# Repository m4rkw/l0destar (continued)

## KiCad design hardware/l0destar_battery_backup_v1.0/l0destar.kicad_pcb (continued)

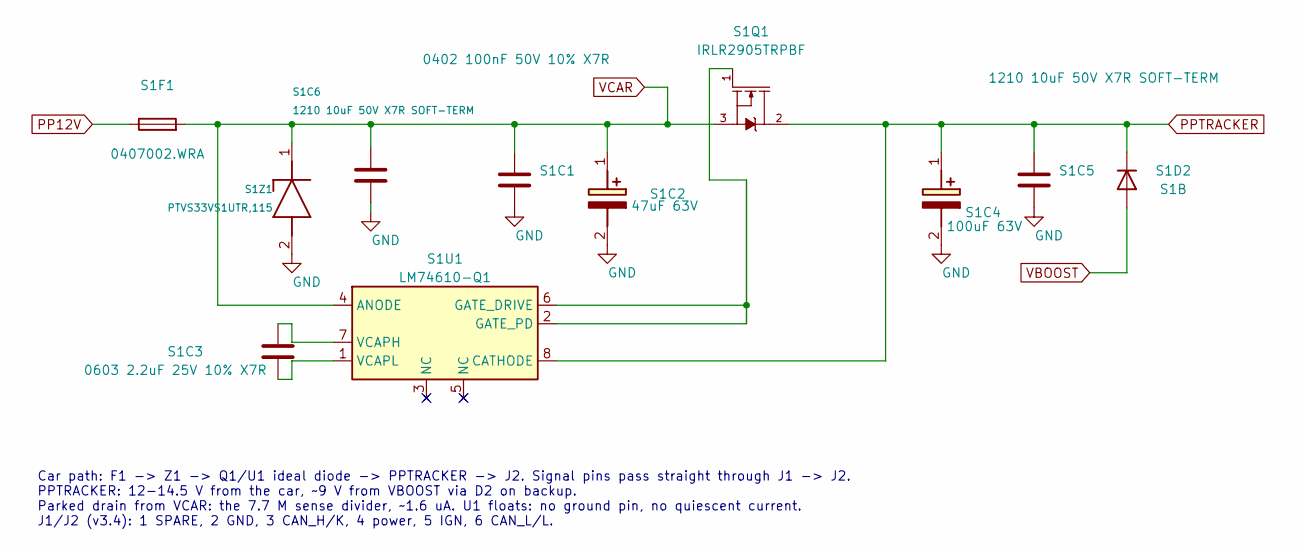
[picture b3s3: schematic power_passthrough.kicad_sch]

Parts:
S1C1: 0402 100nF 50V 10% X7R; C_0402_1005Metric; MPN GRM155R71H104KE14D
S1C2: 47uF 63V; EEE_FK1J470P; MPN EEE-FK1J470P
S1C3: 0603 2.2uF 25V 10% X7R; C_0603_1608Metric; MPN GRM188Z71E225KE43D
S1C4: 100uF 63V; EEEFK1J101P; MPN EEE-FK1J101P
S1C5, S1C6: 1210 10uF 50V X7R SOFT-TERM; C_1210_3225Metric; MPN MCJCU32MLB7106KPPDT1
S1D2: S1B; D_SMA; MPN S1B
S1F1: 0407002.WRA; Fuse_1206_3216Metric; MPN 0407002.WRA
S1Q1: IRLR2905TRPBF
S1U1: LM74610-Q1; VSSOP-8_3x3mm_P0.65mm; MPN LM74610QDGKRQ1
S1Z1: PTVS33VS1UTR,115; Nexperia_CFP3_SOD-123W; MPN PTVS33VS1UTR,115

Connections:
GND: S1C1.2, S1C2.2 (-), S1C4.2 (-), S1C5.2, S1C6.2, S1Z1.2 (A); also elsewhere on the board
unnamed: S1Q1.1, S1U1.2 (GATE_PD), S1U1.6 (GATE_DRIVE)
unnamed: S1C3.1, S1U1.7 (VCAPH)
unnamed: S1C3.2, S1U1.1 (VCAPL)
PP12V: S1F1.1; also elsewhere on the board
PPTRACKER: S1C4.1 (+), S1C5.1, S1D2.1 (K), S1Q1.2, S1Q1.PAD, S1U1.8 (CATHODE); also elsewhere on the board
VBOOST: S1D2.2 (A); also elsewhere on the board
VCAR: S1C1.1, S1C2.1 (+), S1C6.1, S1F1.2, S1Q1.3, S1U1.4 (ANODE), S1Z1.1 (K); also elsewhere on the board

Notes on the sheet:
Car path: F1 -> Z1 -> Q1/U1 ideal diode -> PPTRACKER -> J2. Signal pins pass straight through J1 -> J2. PPTRACKER: 12-14.5 V from the car, ~9 V from VBOOST via D2 on backup. Parked drain from VCAR: the 7.7 M sense divider, ~1.6 uA. U1 floats: no ground pin, no quiescent current. J1/J2 (v3.4): 1 SPA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

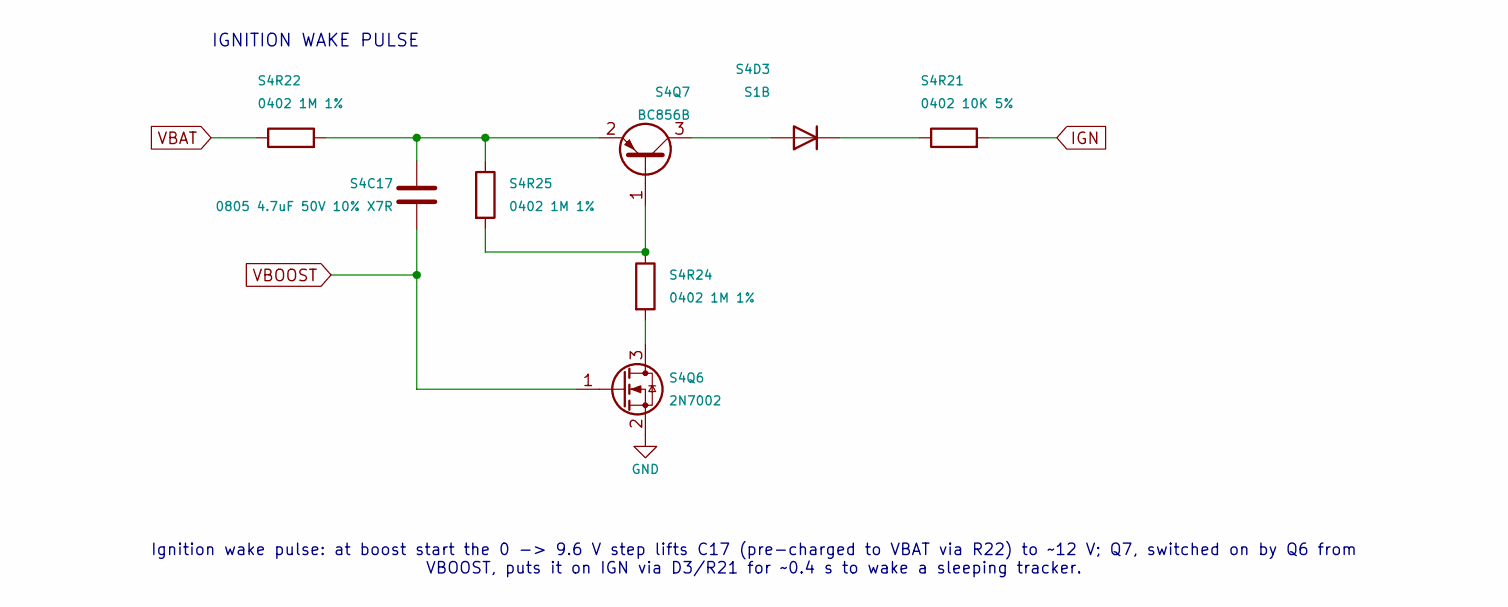
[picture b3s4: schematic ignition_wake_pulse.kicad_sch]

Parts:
S4C17: 0805 4.7uF 50V 10% X7R; C_0805_2012Metric; MPN GRM21BZ71H475KE15K
S4D3: S1B; D_SMA; MPN S1B
S4Q6: 2N7002; SOT-23; MPN 2N7002
S4Q7: BC856B; SOT-23; MPN BC856B
S4R21: 0402 10K 5%; R_0402_1005Metric
S4R22, S4R24, S4R25: 0402 1M 1%; R_0402_1005Metric

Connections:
GND: S4Q6.2 (S); also elsewhere on the board
IGN: S4R21.2; also elsewhere on the board
unnamed: S4D3.2 (A), S4Q7.3 (C)
unnamed: S4D3.1 (K), S4R21.1
unnamed: S4Q6.3 (D), S4R24.2
unnamed: S4Q7.1 (B), S4R24.1, S4R25.2
unnamed: S4C17.1, S4Q7.2 (E), S4R22.2, S4R25.1
VBAT: S4R22.1; also elsewhere on the board
VBOOST: S4C17.2, S4Q6.1 (G); also elsewhere on the board

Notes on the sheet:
IGNITION WAKE PULSE
Ignition wake pulse: at boost start the 0 -> 9.6 V step lifts C17 (pre-charged to VBAT via R22) to ~12 V; Q7, switched on by Q6 from VBOOST, puts it on IGN via D3/R21 for ~0.4 s to wake a sleeping tracker.

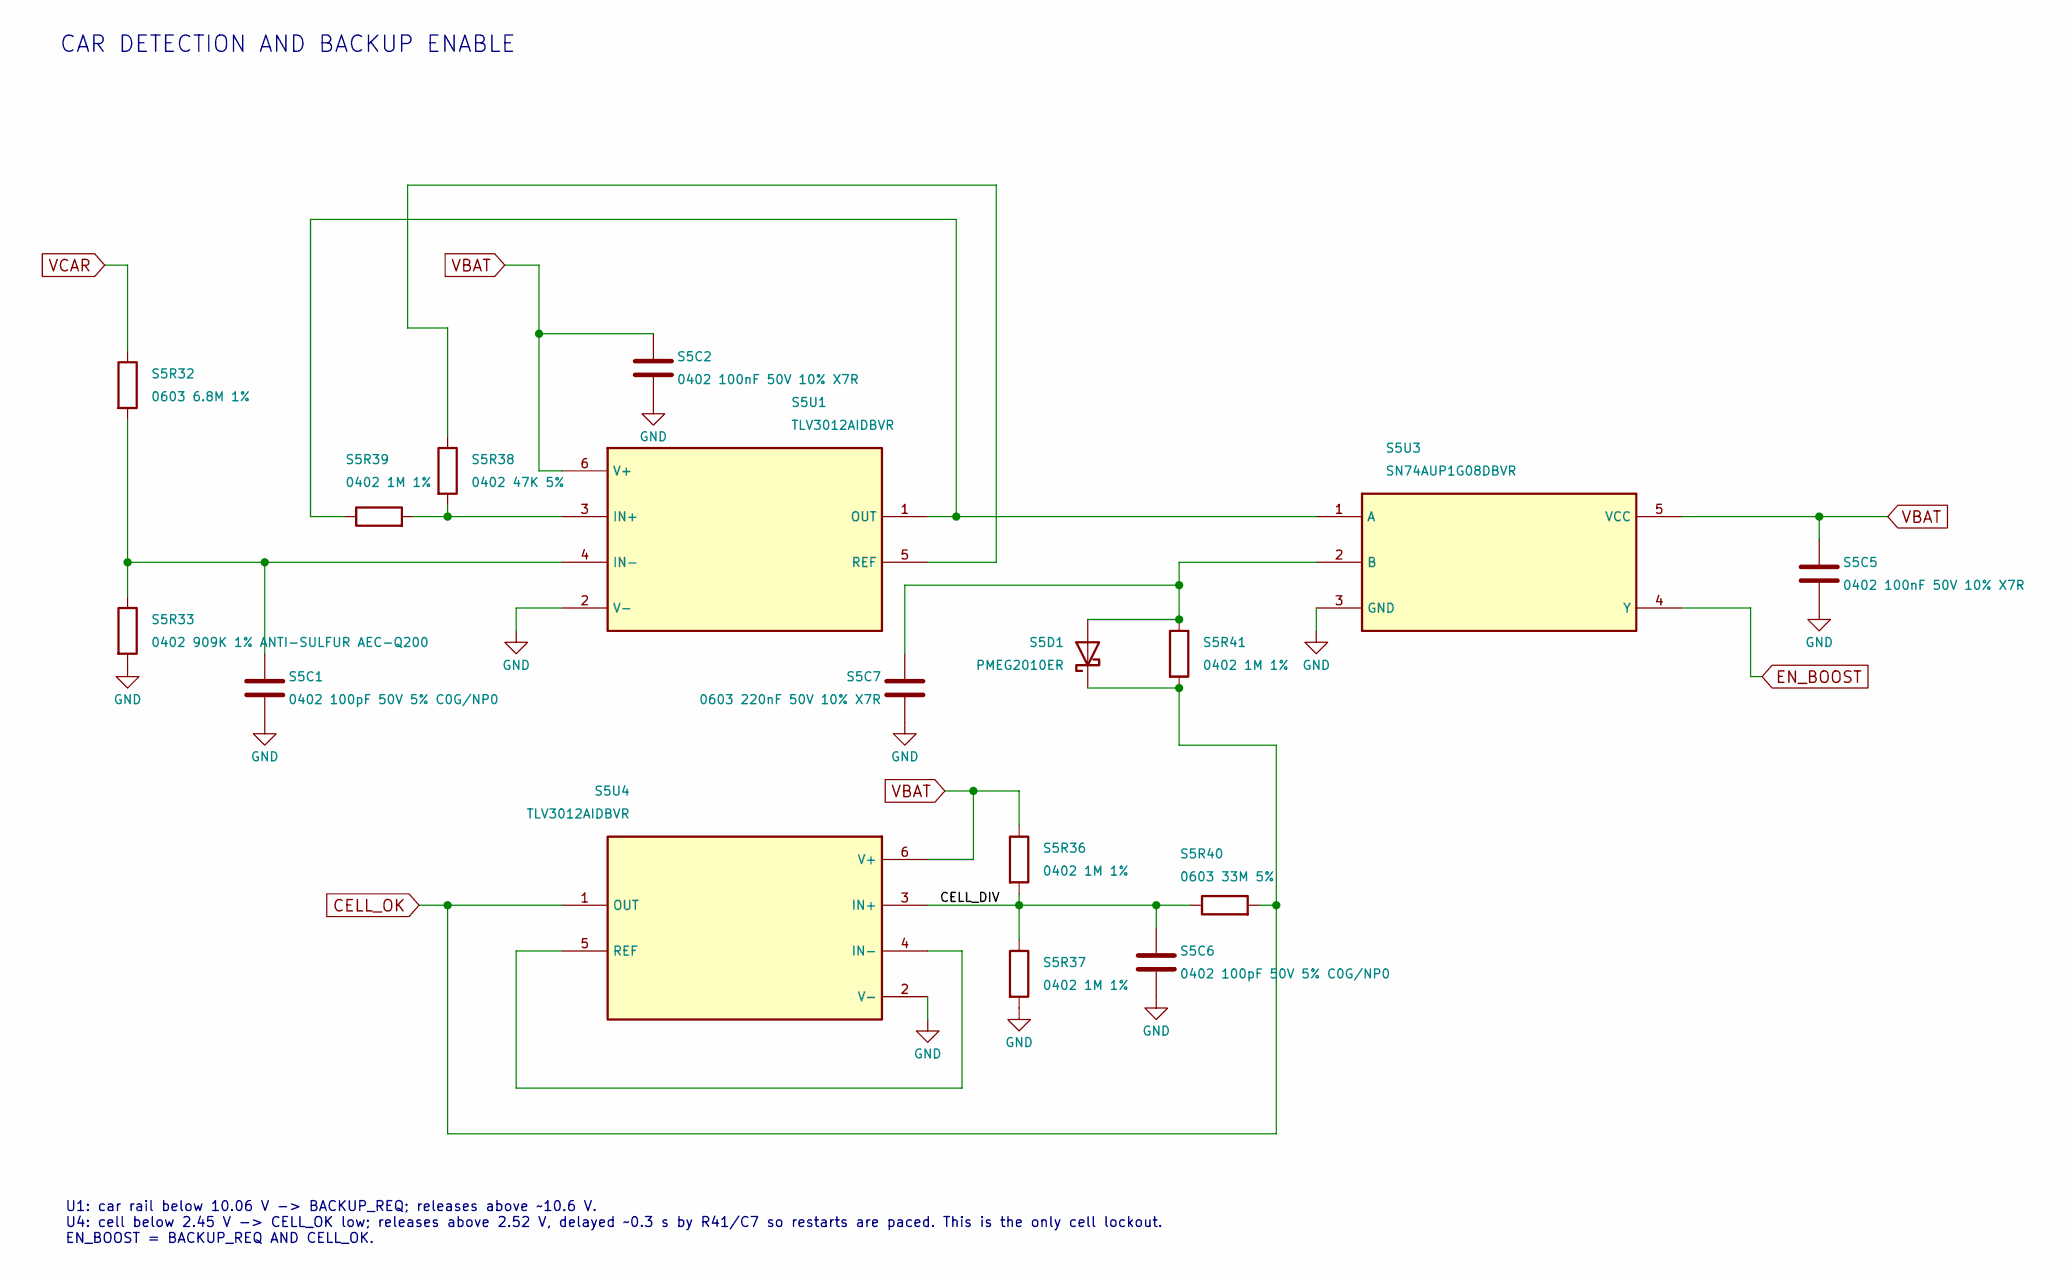
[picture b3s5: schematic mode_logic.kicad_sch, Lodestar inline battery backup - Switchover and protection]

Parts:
S5C1, S5C6: 0402 100pF 50V 5% C0G/NP0; C_0402_1005Metric; MPN 0402N101J500CT
S5C2, S5C5: 0402 100nF 50V 10% X7R; C_0402_1005Metric; MPN GRM155R71H104KE14D
S5C7: 0603 220nF 50V 10% X7R; C_0603_1608Metric
S5D1: PMEG2010ER; Nexperia_CFP3_SOD-123W; MPN PMEG2010ER,115
S5R32: 0603 6.8M 1%; R_0603_1608Metric
S5R33: 0402 909K 1% ANTI-SULFUR AEC-Q200; R_0402_1005Metric; MPN AF0402FR-07909KL
S5R36, S5R37, S5R39, S5R41: 0402 1M 1%; R_0402_1005Metric
S5R38: 0402 47K 5%; R_0402_1005Metric
S5R40: 0603 33M 5%; R_0603_1608Metric
S5U1, S5U4: TLV3012AIDBVR; SOT-23-6; MPN TLV3012AIDBVR
S5U3: SN74AUP1G08DBVR; SOT-23-5; MPN SN74AUP1G08DBVR

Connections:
/Automatic switchover/CELL_DIV: S5C6.1, S5R36.2, S5R37.1, S5R40.1, S5U4.3 (IN+)
CELL_OK: S5D1.1 (K), S5R40.2, S5R41.2, S5U4.1 (OUT)
EN_BOOST: S5U3.4 (Y); also elsewhere on the board
GND: S5C1.2, S5C2.2, S5C5.2, S5C6.2, S5C7.2, S5R33.2, S5R37.2, S5U1.2 (V-), S5U3.3 (GND), S5U4.2 (V-); also elsewhere on the board
unnamed: S5C7.1, S5D1.2 (A), S5R41.1, S5U3.2 (B)
unnamed: S5R38.2, S5R39.2, S5U1.3 (IN+)
unnamed: S5C1.1, S5R32.2, S5R33.1, S5U1.4 (IN-)
unnamed: S5R39.1, S5U1.1 (OUT), S5U3.1 (A)
unnamed: S5R38.1, S5U1.5 (REF)
unnamed: S5U4.4 (IN-), S5U4.5 (REF)
VBAT: S5C2.1, S5C5.1, S5R36.1, S5U1.6 (V+), S5U3.5 (VCC), S5U4.6 (V+); also elsewhere on the board
VCAR: S5R32.1; also elsewhere on the board

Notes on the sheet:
CAR DETECTION AND BACKUP ENABLE
U1: car rail below 10.06 V -> BACKUP_REQ; releases above ~10.6 V. U4: cell below 2.45 V -> CELL_OK low; releases above 2.52 V, delayed ~0.3 s by R41/C7 so restarts are paced. This is the only cell lockout. EN_BOOST = BACKUP_REQ AND CELL_OK.

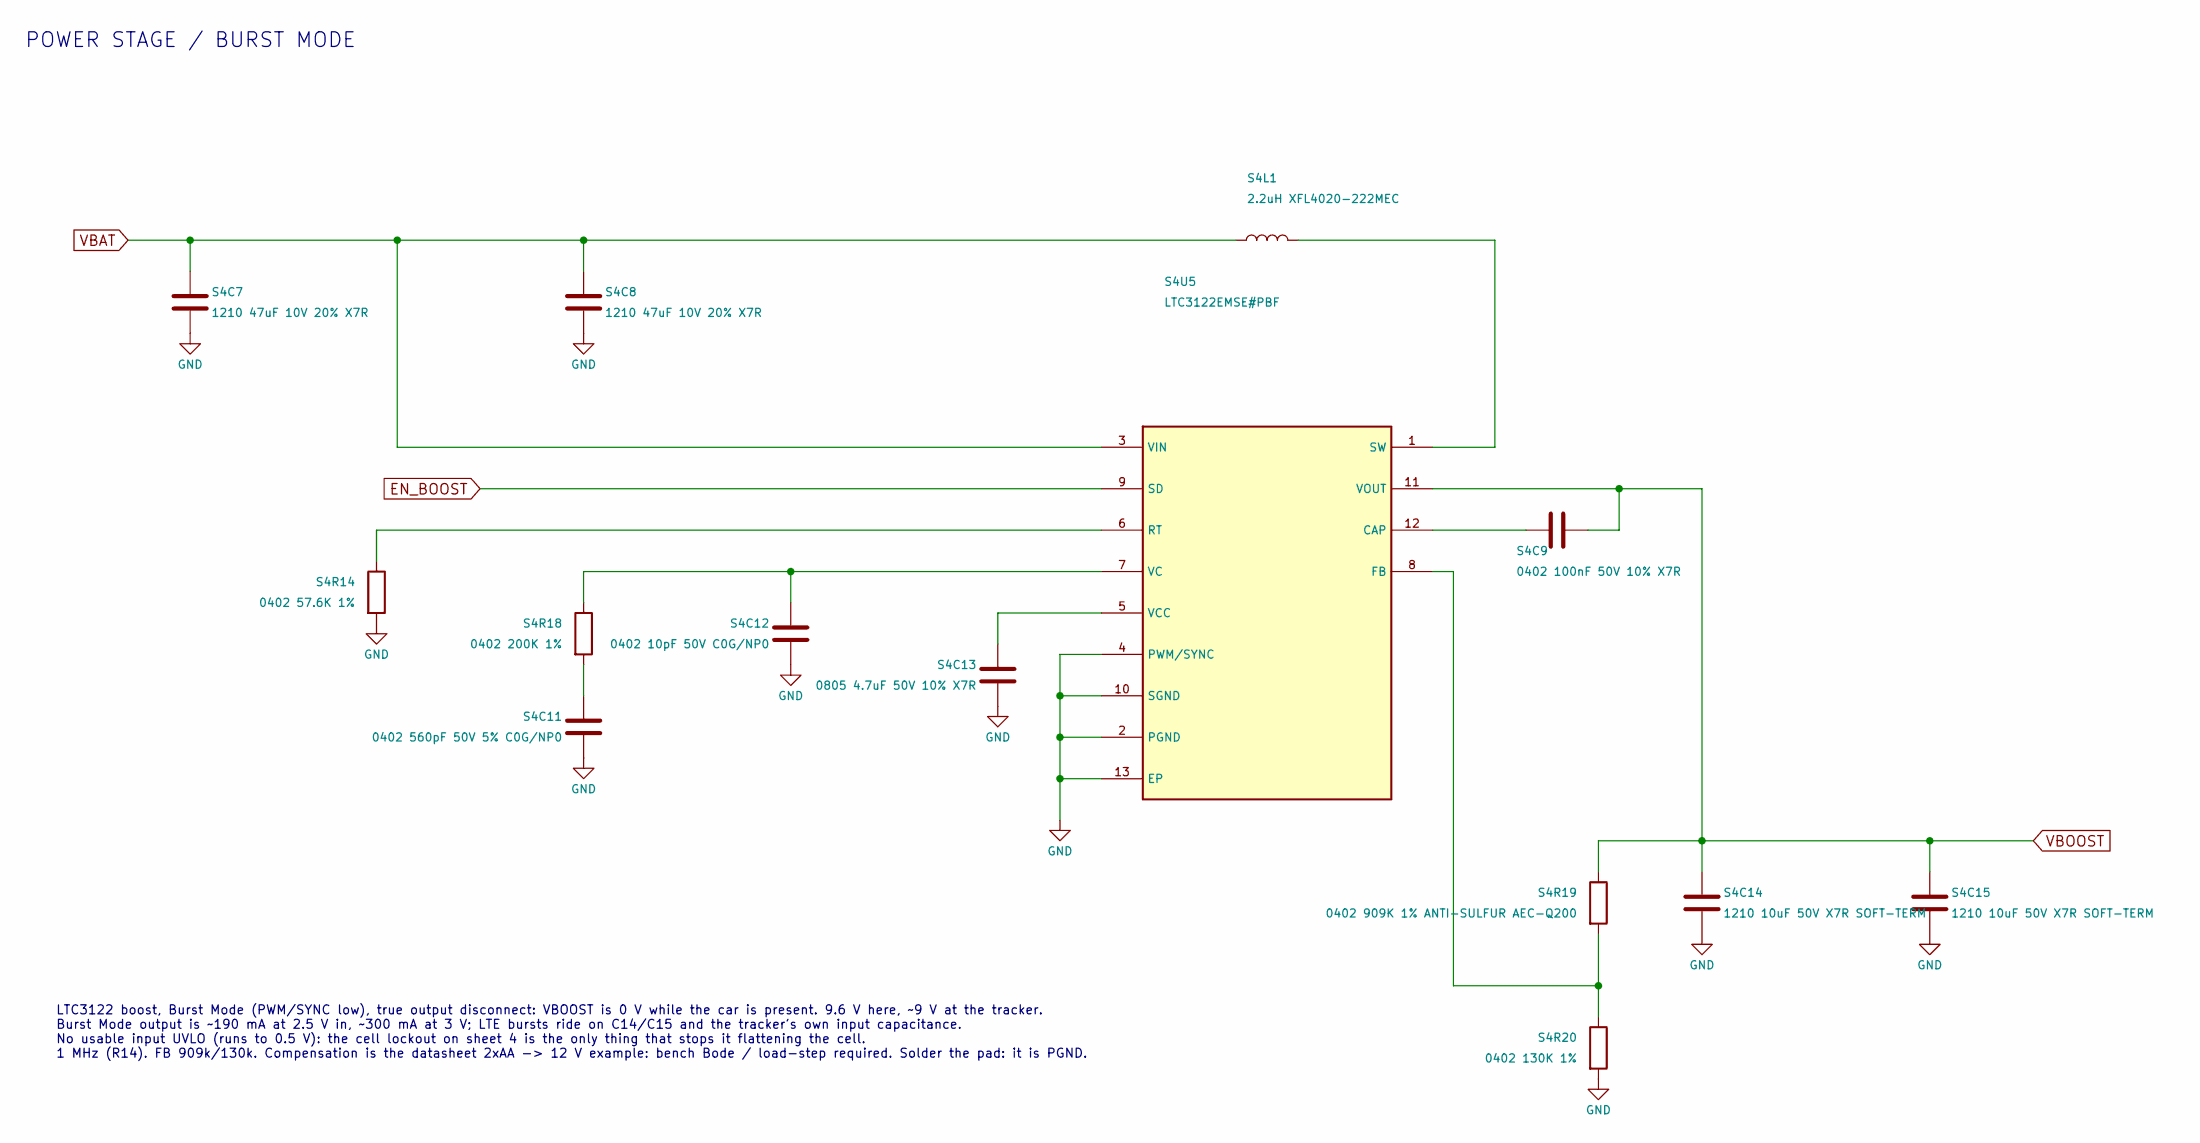
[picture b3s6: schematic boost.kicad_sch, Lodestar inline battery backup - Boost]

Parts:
S4C7, S4C8: 1210 47uF 10V 20% X7R; C_1210_3225Metric; MPN CL32B476MPJNNNE
S4C9: 0402 100nF 50V 10% X7R; C_0402_1005Metric; MPN GRM155R71H104KE14D
S4C11: 0402 560pF 50V 5% C0G/NP0; C_0402_1005Metric
S4C12: 0402 10pF 50V C0G/NP0; C_0402_1005Metric; MPN GRM1555C1H100JA01D
S4C13: 0805 4.7uF 50V 10% X7R; C_0805_2012Metric; MPN GRM21BZ71H475KE15K
S4C14, S4C15: 1210 10uF 50V X7R SOFT-TERM; C_1210_3225Metric; MPN MCJCU32MLB7106KPPDT1
S4L1: 2.2uH XFL4020-222MEC; IND_XFL4020-222ME; MPN XFL4020-222MEC
S4R14: 0402 57.6K 1%; R_0402_1005Metric
S4R18: 0402 200K 1%; R_0402_1005Metric
S4R19: 0402 909K 1% ANTI-SULFUR AEC-Q200; R_0402_1005Metric; MPN AF0402FR-07909KL
S4R20: 0402 130K 1%; R_0402_1005Metric
S4U5: LTC3122EMSE#PBF; MSOP-12-1EP_3x4.039mm_P0.65mm_EP1.651x2.845mm; MPN LTC3122EMSE#PBF

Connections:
EN_BOOST: S4U5.9 (SD); also elsewhere on the board
GND: S4C7.2, S4C8.2, S4C11.2, S4C12.2, S4C13.2, S4C14.2, S4C15.2, S4R14.2, S4R20.2, S4U5.2 (PGND), S4U5.4 (PWM/SYNC), S4U5.10 (SGND), S4U5.13 (EP); also elsewhere on the board
unnamed: S4C11.1, S4R18.2
unnamed: S4C9.1, S4U5.12 (CAP)
unnamed: S4R19.2, S4R20.1, S4U5.8 (FB)
unnamed: S4R14.1, S4U5.6 (RT)
unnamed: S4L1.2, S4U5.1 (SW)
unnamed: S4C12.1, S4R18.1, S4U5.7 (VC)
unnamed: S4C13.1, S4U5.5 (VCC)
VBAT: S4C7.1, S4C8.1, S4L1.1, S4U5.3 (VIN); also elsewhere on the board
VBOOST: S4C9.2, S4C14.1, S4C15.1, S4R19.1, S4U5.11 (VOUT); also elsewhere on the board

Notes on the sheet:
LTC3122 boost, Burst Mode (PWM/SYNC low), true output disconnect: VBOOST is 0 V while the car is present. 9.6 V here, ~9 V at the tracker. Burst Mode output is ~190 mA at 2.5 V in, ~300 mA at 3 V; LTE bursts ride on C14/C15 and the tracker's own input capacitance. No usable input UVLO (runs to 0.5 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
POWER STAGE / BURST MODE

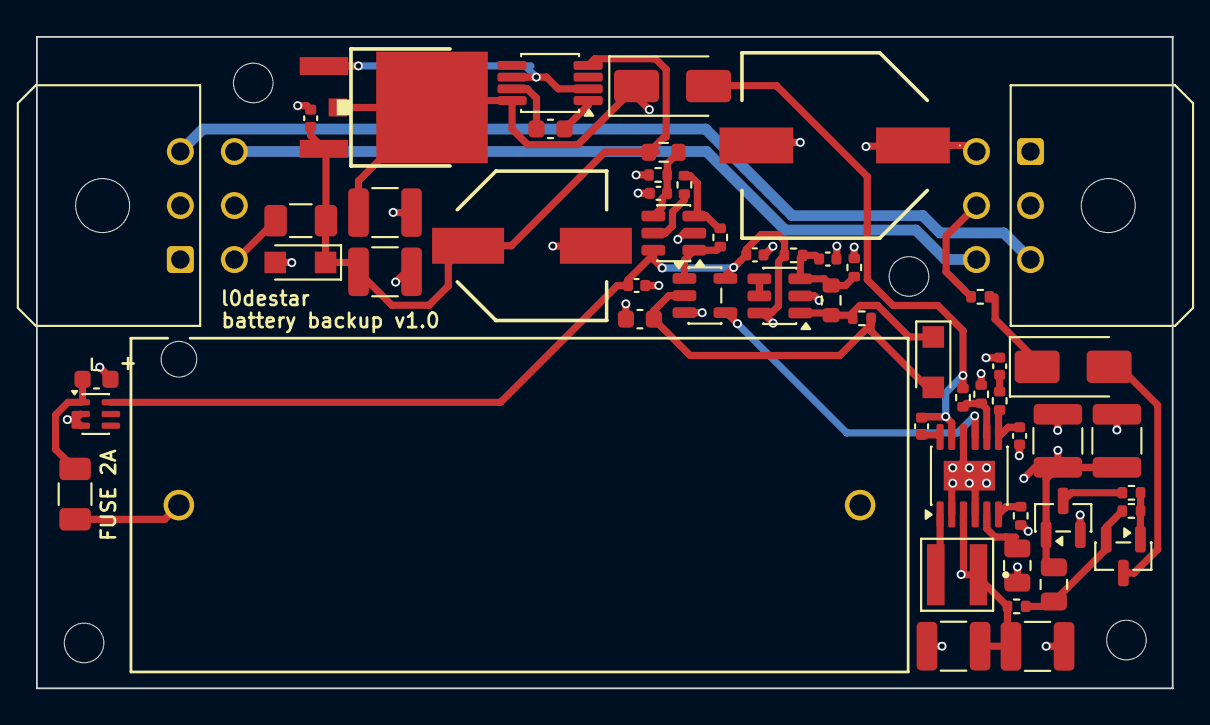
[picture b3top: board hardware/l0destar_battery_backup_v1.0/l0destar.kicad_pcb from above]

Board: 4 copper layers, 63.1 x 36.2 mm, 60 parts (0 on the bottom side), 35 nets.

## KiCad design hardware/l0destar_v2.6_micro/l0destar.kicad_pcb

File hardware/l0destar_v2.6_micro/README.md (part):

# l0destar v2.6 micro

## Overview

- This is a prototype l0destar vehicle tracker PCB designed to be
  hand-solderable (hot air required)
- It makes use of the [Makerdiary nRF9151 Connect Kit](https://makerdiary.com/products/nrf9151-connectkit) to provide the LTE and GPS
functions
- Component vias are dogleg-routed deliberately in order to keep the PCB costs
as low as possible
- The RF trace width is calculated using a standard 4-layer stackup at JLCPCB,
  different fabrication processes may require adjustment

## Disclaimer

This is a prototype, not a product. Nothing here is validated or certified,
the parts lists are examples rather than a verified BOM, and any test results
recorded below are my own unverified bench observations - repeat the testing
yourself rather than taking them on trust.

**Before building or installing anything from this repository, read the
[full disclaimer](../../DISCLAIMER.md).**

## Test status

| Item | Test | Result | Notes |
|---------|------|--------|-------|
| Input stage | 12V input reverse polarity | PASSED | |
| Input stage | 12V ignition input reverse polarity | PASSED | |
| INA228 | Voltage reading function | PASSED |
| Ignition presence | Ignition sense 3.3v signal | PASSED | |
| LT8609 | 4.2V output | PASSED | |
| Auxillary 3.3V rail | Switches on enable signal | PASSED | |
| Accelerometer | Operates while awake | PASSED | |
| Accelerometer | Wake on motion | PASSED | |
| GPS antenna bias tee | Obtains GPS signal | PASSED | |
| Board | Quiescent current | 120 µA | |

## Features

 - 12V live and 12V ignition inputs with TVS and reverse polarity protection
 - Ignition presence sensing
 - INA228 voltage reading
 - High efficiency buck converter
 - Auxillary 3.3V rail for the GPS antenna bias tee
 - ASM330LHHXG1TR 6-axis IMU gyro/accelerometer
 - USB-C can be connected and disconnected for programming without any power
   disruption

## Changes from v2.5

 - Added stacked 47uF ceramic bulk on the 12V input to provide additional
   resilience against automotive transient spikes

## Power supply

The Connect Kit can be powered through VBUS which would be much simpler as it
can take 5V, but then you have to disconnect the power before connecting a USB
cable. Same for the Nordic dev board - they both explicitly say not to connect
powered USB and VBUS at the same time. Because the intention is to install this
in a vehicle for testing the pragmatic decision was taken to power it with a
4.2V buck feeding the battery connector. With this power connection we can
connect USB-C at any time to update the firmware without needing to disconnect
power.

## Bill of materials

| Item | Description | Specification | Example | Notes |
|------|-------------|---------------|---------|-------|
| MCU | MCU and GSM/GPS 40pin board | nRF9151 Connect Kit | [Makerdiary nRF9151 Connect Kit](https://makerdiary.com/products/nrf9151-connectkit) | |
| S1J1 | Molex Micro-fit 3.0 2x02 PCB connector | 43045-0400 | [43045-0400](https://uk.farnell.com/molex/43045-0400/conn-r-a-pcb-hdr-4pos-2row-3mm/dp/9733019) | | 
| S1J2 | Makerdiary header 1 | 20-pin 2.54mm header | [20-pin pcb header](https://amzn.to/44hTFGN) | |
| S1J3 | Makerdiary header 2 | 20-pin 2.54mm header | [20-pin pcb header](https://amzn.to/44hTFGN) | |
| S1R1 | I2C pull-up resistor | 0402 4.7K 1% | [MP003476](https://uk.farnell.com/multicomp-pro/mp003476/res-4k7-1-0-0625w-0402-thick-film/dp/3392645) | |
| S1R2 | I2C pull-up resistor | 0402 4.7K 1% | [MP003476](https://uk.farnell.com/multicomp-pro/mp003476/res-4k7-1-0-0625w-0402-thick-film/dp/3392645) | |
| S1C1 | 220uF buck output capacitor | 1210 220uF 6.3V 20% X5R | [GRM32ER60J227ME05K](https://uk.farnell.com/murata/grm32er60j227me05k/cap-220-f-6-3v-20-x5r-1210/dp/2671587) | Higher voltage/X7R spec is better if available |
| S1C2 | 220uF buck output capacitor | 1210 220uF 6.3V 20% X5R | [GRM32ER60J227ME05K](https://uk.farnell.com/murata/grm32er60j227me05k/cap-220-f-6-3v-20-x5r-1210/dp/2671587) | Higher voltage/X7R spec is better if available |
| S2Q1 | Reverse-polarity MOSFET | SQ2361 SOT-23 | [SQ2361ES-T1_GE3](https://uk.farnell.com/vishay/sq2361es-t1-ge3/mosfet-aec-q101-p-ch-60v-sot-23/dp/2889711) | |
| S2Q2 | Reverse-polarity MOSFET | SQ2361 SOT-23 | [SQ2361ES-T1_GE3](https://uk.farnell.com/vishay/sq2361es-t1-ge3/mosfet-aec-q101-p-ch-60v-sot-23/dp/2889711) | |
| S2D1 | 15V Zener diode | BZX84C15 | [BZX84C15](https://uk.farnell.com/multicomp-pro/bzx84c15/zener-diode-0-3w-15v-sot-23/dp/2675186) | |
| S2D2 | 400W TVS diode | PTVS33VS1UTR,115 SOD-123W | [PTVS33VS1UTR,115](https://uk.farnell.com/nexperia/ptvs33vs1utr-115/tvs-diode-aecq101-unidir-33v-400w/dp/3440137) | |
| S2D3 | 15V Zener diode | BZX84C15 | [BZX84C15](https://uk.farnell.com/multicomp-pro/bzx84c15/zener-diode-0-3w-15v-sot-23/dp/2675186) | |
| S2D4 | 400W TVS diode | PTVS33VS1UTR,115 SOD-123W | [PTVS33VS1UTR,115](https://uk.farnell.com/nexperia/ptvs33vs1utr-115/tvs-diode-aecq101-unidir-33v-400w/dp/3440137) | |
| S2R1 | Pulldown resistor | 0402 1% 1M | [ERJ2RKF1004X](https://uk.farnell.com/panasonic/erj2rkf1004x/res-1m-1-0-1w-0402-thick-film/dp/2302957) | |
| S2R2 | Pulldown resistor | 0402 1% 1M | [ERJ2RKF1004X](https://uk.farnell.com/panasonic/erj2rkf1004x/res-1m-1-0-1w-0402-thick-film/dp/2302957) | |
| S2C1 | 47uF input capacitor | 2220 >= 50V 20% X7R | [CKG57NX7R1H476M500JH](https://uk.farnell.com/tdk/ckg57nx7r1h476m500jh/cap-stacked-47uf-50v-mlcc-2220/dp/3816888) | |
| S3U1 | INA228 voltage read IC | INA228 10-VSSOP | [INA228](https://www.aliexpress.com/item/1005008704299153.html) | |
| S3C1 | 1uF capacitor | 0402 >= 10V 10% X7R | [KAM05CR71A105KH](https://uk.farnell.com/kyocera-avx/kam05cr71a105kh/capacitor-mlcc-1uf-x7r-10v-0402/dp/4365709) | |
| S3C2 | 100nF capacitor | 0402 >= 25V 10% X7R | [MC0402B104K250CT](https://uk.farnell.com/multicomp-pro/mc0402b104k250ct/cap-0-1-f-25v-10-x7r-0402/dp/2320759) | |
| S4Q1 | Ignition sense MOSFET | 2N7002 SOT-23 | [2N7002](https://uk.farnell.com/multicomp-pro/2n7002/mosfet-n-ch-60v-0-115a-sot-23/dp/4295174) | |
| S4R1 | Ignition sense resistor | 0402 120K 1% | [RC0402FR-07120KL](https://uk.farnell.com/yageo/rc0402fr-07120kl/res-120k-1-0-063w-0402-thick-film/dp/9239480) | |
| S4R2 | Ignition sense resistor | 0402 47K 1% | [ERJ2RKF4702X](https://uk.farnell.com/panasonic/erj2rkf4702x/res-47k-1-0-1w-0402-thick-film/dp/2302806) | |
| S4R3 | Ignition sense resistor | 0402 56K 1% | [MCMR04X5602FTL](https://uk.farnell.com/multicomp-pro/mcmr04x5602ftl/res-56k-1-0-0625w-0402-ceramic/dp/2073131) | |
| S4C1 | 100nF capacitor | 0402 >= 25V 10% X7R | [MC0402B104K250CT](https://uk.farnell.com/multicomp-pro/mc0402b104k250ct/cap-0-1-f-25v-10-x7r-0402/dp/2320759) | |
| S6U1 | Buck converter | LT8609AIMSE MSOP-EP-10 | [LT8609AIMSE#PBF](https://uk.farnell.com/analog-devices/lt8609aimse-pbf/dc-dc-conv-sync-buck-2mhz-125deg/dp/4025049) | |
| S6U2 | Ideal diode | LM66100 | [LM66100](https://www.aliexpress.com/item/1005008565117953.html) | |
| S6L1 | Inductor | XFL4020-222ME | [XFL4020-222MEC](https://uk.farnell.com/coilcraft/xfl4020-222mec/inductor-2-2uh-8a-20-pwr-38mhz/dp/2289216) | |
| S6C1 | 100nF capacitor | 0402 >= 25V 10% X7R | [MC0402B104K250CT](https://uk.farnell.com/multicomp-pro/mc0402b104k250ct/cap-0-1-f-25v-10-x7r-0402/dp/2320759) | |
| S6C2 | 1uF capacitor | 0402 >= 10V 10% X7R | [KAM05CR71A105KH](https://uk.farnell.com/kyocera-avx/kam05cr71a105kh/capacitor-mlcc-1uf-x7r-10v-0402/dp/4365709) | |
| S6C3 | 4.7uF capacitor | 0805 >= 50V 10% X7R | [GRM21BZ71H475KE15K](https://uk.farnell.com/murata/grm21bz71h475ke15k/cap-4-7uf-50v-mlcc-0805/dp/3582887) | |
| S6C4 | 10pF capacitor | 0402 >= 25V 10% X7R | [C0402C100K5RACTU](https://uk.farnell.com/kemet/c0402c100k5ractu/cap-10pf-50v-10-x7r-0402/dp/2821254) | |
| S6C5 | 22uF capacitor | 0805 >= 10V 20% X7T | [GCM21BD71A226MEC4L](https://uk.farnell.com/murata/gcm21bd71a226mec4l/cap-mlcc-22uf-x7t-10v-0805/dp/4813843) | Higher voltage rating/X7R is better if available |
| S6R1 | Oscillator frequency resistor | 0402 18.2K 1% | [RC0402FR-0718K2L](https://uk.farnell.com/yageo/rc0402fr-0718k2l/res-18k2-1-0-0625w-0402-thick/dp/3495542) | 18.2K == 2MHz |
| S6R2 | Output voltage divider resistor | 0402 226K 1% | [MCMR04X2263FTL](https://uk.farnell.com/multicomp-pro/mcmr04x2263ftl/res-226k-1-0-0625w-0402-ceramic/dp/2072796) | VOUT == 0.782V x (1 + S6R3/S6R2) == 4.24V |
| S6R3 | Output voltage divider resistor | 0402 1M 1% | [ERJ2RKF1004X](https://uk.farnell.com/panasonic/erj2rkf1004x/res-1m-1-0-1w-0402-thick-film/dp/2302957) | VOUT == 0.782V x (1 + S6R3/S6R2) == 4.24V |
| S7Q1 | Aux power MOSFET | 2N7002 SOT-23 | [2N7002](https://uk.farnell.com/multicomp-pro/2n7002/mosfet-n-ch-60v-0-115a-sot-23/dp/4295174) | |
| S7Q2 | Aux power MOSFET | DMG3415U SOT-23 | [DMG3415UQ-7](https://uk.farnell.com/diodes-inc/dmg3415uq-7/mosfet-p-ch-20v-4a-sot-23/dp/3943490) | |
| S7R1 | Aux power resistor | 0402 100K 1% | [MCPWR02FTEP1003A](https://uk.farnell.com/multicomp-pro/mcpwr02ftep1003a/res-100k-1-thick-film-0402/dp/4538624) | |
| S7R2 | Aux power resistor | 0402 1M 1% | [ERJ2RKF1004X](https://uk.farnell.com/panasonic/erj2rkf1004x/res-1m-1-0-1w-0402-thick-film/dp/2302957) | |
| S7R3 | Aux power resistor | 0402 100K 1% | [MCPWR02FTEP1003A](https://uk.farnell.com/multicomp-pro/mcpwr02ftep1003a/res-100k-1-thick-film-0402/dp/4538624) | |
| S7R4 | Aux power resistor | 0402 470K 1% | [ERJ2RKF4703X](https://uk.farnell.com/panasonic/erj2rkf4703x/res-470k-1-0-1w-0402-thick-film/dp/2302916) | |
| S8U1 | ASM330LHHXTR accelerometer | ASM330LHHXTR | [ASM330LHHXTR](https://estore.st.com/en/products/mems-and-sensors/inemo-inertial-modules/asm330lhhx.html) | |
| S8C1 | 100nF capacitor | 0402 >= 25V 10% X7R | [MC0402B104K250CT](https://uk.farnell.com/multicomp-pro/mc0402b104k250ct/cap-0-1-f-25v-10-x7r-0402/dp/2320759) | |
| S8C2 | 10uF capacitor | 0603 >= 6.3V 20% X7T | [GRT188D71A106ME13D](https://uk.farnell.com/murata/grt188d71a106me13d/cap-mlcc-10uf-x7t-10v-0603/dp/4335734) | Higher voltage/X7R is better if available |
| S8C3 | 100nF capacitor | 0402 >= 25V 10% X7R | [MC0402B104K250CT](https://uk.farnell.com/multicomp-pro/mc0402b104k250ct/cap-0-1-f-25v-10-x7r-0402/dp/2320759) | |
| S13R1 | LED resistor | 0402 1K 1% | [CRCW04021K00FKED](https://uk.farnell.com/vishay/crcw04021k00fked/res-1k-1-0-063w-0402-thick-film/dp/1469662) | |
| S13R2 | LED resistor | 0402 1K 1% | [CRCW04021K00FKED](https://uk.farnell.com/vishay/crcw04021k00fked/res-1k-1-0-063w-0402-thick-film/dp/1469662) | |
| S13R3 | LED resistor | 0402 1K 1% | [CRCW04021K00FKED](https://uk.farnell.com/vishay/crcw04021k00fked/res-1k-1-0-063w-0402-thick-film/dp/1469662) | |
| S13D1 | Status LED | 0603 | [MP001249](https://uk.farnell.com/multicomp-pro/mp001249/led-red-385mcd-629nm-0603/dp/3265380) | |
| S13D2 | Status LED | 0603 | [MP001249](https://uk.farnell.com/multicomp-pro/mp001249/led-red-385mcd-629nm-0603/dp/3265380) | |
| S13D3 | Status LED | 0603 | [MP001249](https://uk.farnell.com/multicomp-pro/mp001249/led-red-385mcd-629nm-0603/dp/3265380) | |
| S15J1 | u.FL PCB connector | 50 ohm | [U.FL-R-SMT(01)](https://uk.farnell.com/hirose-hrs/u-fl-r-smt-01/rf-coaxial-u-fl-straight-jack/dp/3908021) | |
| S15J2 | SMA PCB connector | 50 ohm | [SMA-J-P-H-RA-TH1](https://uk.farnell.com/samtec/sma-j-p-h-ra-th1/rf-coaxial-sma-jack-50-ohm-pcb/dp/2856817) | |
| S15J3 | u.FL PCB connector | 50 ohm | [U.FL-R-SMT(01)](https://uk.farnell.com/hirose-hrs/u-fl-r-smt-01/rf-coaxial-u-fl-straight-jack/dp/3908021) | |
| S15J4 | SMA PCB connector | 50 ohm | [SMA-J-P-H-RA-TH1](https://uk.farnell.com/samtec/sma-j-p-h-ra-th1/rf-coaxial-sma-jack-50-ohm-pcb/dp/2856817) | |
| S15U1 | Ideal diode | LM66100 | [LM66100](https://www.aliexpress.com/item/1005008565117953.html) | |
| S15FB1 | Ferrite bead | 600 ohm | [BLM15PX601SZ1D](https://uk.farnell.com/murata/blm15px601sz1d/ferrite-bead-0-9a-0-23ohm-0402/dp/3678458) | |
| S15L1 | RF inductor | 0603 47-100 nH, SRF > 2GHz | [LQW18AN68NJ00D](https://uk.farnell.com/murata/lqw18an68nj00d/inductor-68nh-2-2ghz-0-34a-0603/dp/3471533) | |
| S15C1 | 100pF RF capacitor | 0402 >= 25V 1% C0G / NP0 | [AC0402FRNPO9BN101](https://uk.farnell.com/yageo/ac0402frnpo9bn101/cap-100pf-50v-mlcc-0402/dp/4166091) | |
| S15C2 | 100pF RF capacitor | 0402 >= 25V 1% C0G / NP0 | [AC0402FRNPO9BN101](https://uk.farnell.com/yageo/ac0402frnpo9bn101/cap-100pf-50v-mlcc-0402/dp/4166091) | |
| S15C3 | 10nF RF capacitor | 0402 >= 25V 5% C0G / NP0 | [GRM1555CYA103JE01D](https://uk.farnell.com/murata/grm1555cya103je01d/cap-mlcc-0-01uf-c0g-np0-35v-0402/dp/4792250) | |
| S15C4 | 1uF RF capacitor | 0402 >= 25V 10% X7R | [KAM05CR71A105KH](https://uk.farnell.com/kyocera-avx/kam05cr71a105kh/capacitor-mlcc-1uf-x7r-10v-0402/dp/4365709) | |
| - | u.FL cable - LTE | 50 ohm 35mm | [U.FL-2LPHF6-04N1TV-A-35](https://uk.farnell.com/hirose-hrs/u-fl-2lphf6-04n1tv-a-35/cbl-assy-u-fl-r-a-plug-r-a-plug/dp/4294251) | |
| - | u.FL cable - GPS | 50 ohm 35mm | [U.FL-2LPHF6-04N1TV-A-35](https://uk.farnell.com/hirose-hrs/u-fl-2lphf6-04n1tv-a-35/cbl-assy-u-fl-r-a-plug-r-a-plug/dp/4294251) | |
| - | JST power cable | Ultra-thin MX1.25 51146 | [10PCS MX1.25 51146 Cable](https://www.aliexpress.com/item/4000586964114.html) | |

## Parts list

| Item | Quantity | Specification | Example | Notes |
|------|----------|---------------|---------|-------|
| MCU and GSM/GPS 40pin board | 1 | nRF9151 Connect Kit | [Makerdiary nRF9151 Connect Kit](https://makerdiary.com/products/nrf9151-connectkit) | |
| Molex Micro-fit 3.0 2x02 PCB connector | 1 | 43045-0400 | [43045-0400](https://uk.farnell.com/molex/43045-0400/conn-r-a-pcb-hdr-4pos-2row-3mm/dp/9733019) | | 
| 20pin header | 2 | 20-pin 2.54mm header | [20-pin pcb header](https://amzn.to/44hTFGN) | |
| 1K 0402 resistor | 3 | 0402 1K 1% | [CRCW04021K00FKED](https://uk.farnell.com/vishay/crcw04021k00fked/res-1k-1-0-063w-0402-thick-film/dp/1469662) | |
| 4.7K 0402 resistor | 2 | 0402 4.7K 1% | [MP003476](https://uk.farnell.com/multicomp-pro/mp003476/res-4k7-1-0-0625w-0402-thick-film/dp/3392645) | |
| 18.2K 0402 resistor | 1 | 0402 18.2K 1% | [RC0402FR-0718K2L](https://uk.farnell.com/yageo/rc0402fr-0718k2l/res-18k2-1-0-0625w-0402-thick/dp/3495542) | 18.2K == 2MHz |
| 47K 0402 resistor | 1 | 0402 47K 1% | [ERJ2RKF4702X](https://uk.farnell.com/panasonic/erj2rkf4702x/res-47k-1-0-1w-0402-thick-film/dp/2302806) | |
| 56K 0402 resistor | 1 | 0402 56K 1% | [MCMR04X5602FTL](https://uk.farnell.com/multicomp-pro/mcmr04x5602ftl/res-56k-1-0-0625w-0402-ceramic/dp/2073131) | |
| 100K 0402 resistor | 2 | 0402 100K 1% | [MCPWR02FTEP1003A](https://uk.farnell.com/multicomp-pro/mcpwr02ftep1003a/res-100k-1-thick-film-0402/dp/4538624) | |
| 120K 0402 resistor | 1 | 0402 120K 1% | [RC0402FR-07120KL](https://uk.farnell.com/yageo/rc0402fr-07120kl/res-120k-1-0-063w-0402-thick-film/dp/9239480) | |
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
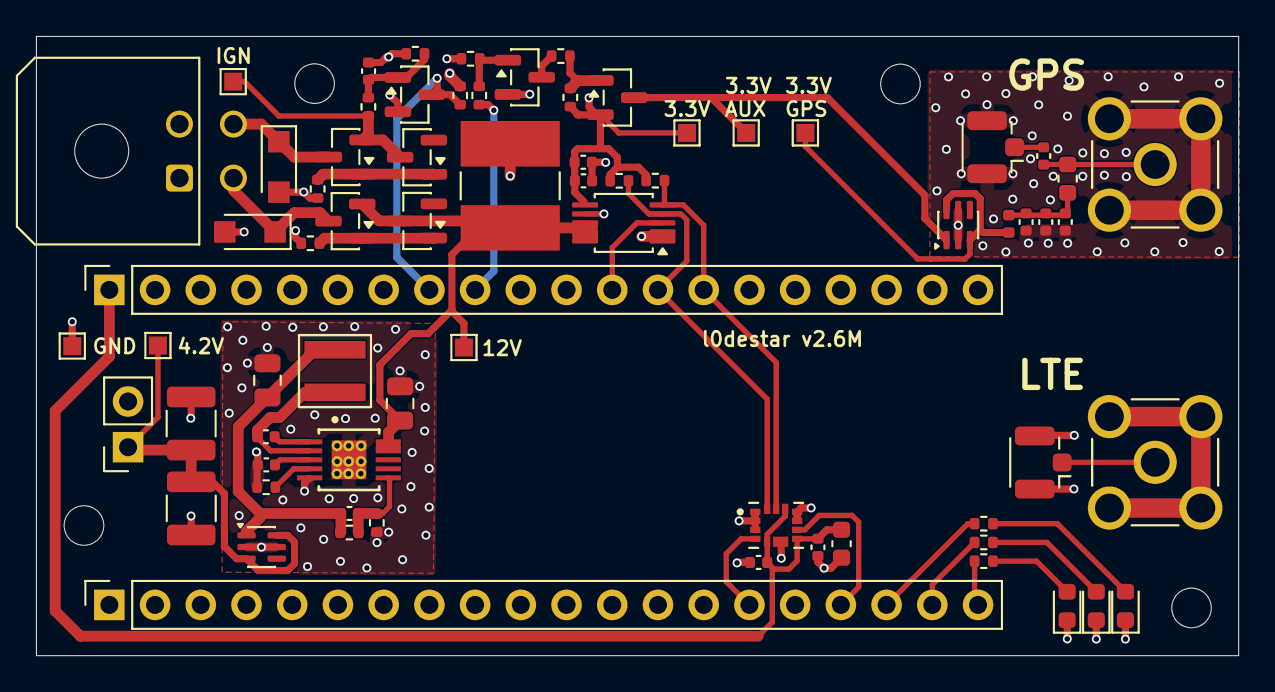
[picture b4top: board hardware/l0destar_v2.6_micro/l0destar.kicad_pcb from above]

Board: 4 copper layers, 66.8 x 34.4 mm, 74 parts (0 on the bottom side), 38 nets.

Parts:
GND1: TestPoint; TestPoint_Pad_1.0x1.0mm
H1, H2, H3, H4: MountingHole; MountingHole_2.2mm_M2
PP3V3, PP3V3AUX1, PP3V3GPS2, PP4V5, PP12VIP1, PP12VP1: TestPoint; TestPoint_Pad_1.0x1.0mm
S1C1, S1C2: 220uF; C_1210_3225Metric
S1J1: Main connector; Molex_Micro-Fit_3.0_43045-0400_2x02_P3.00mm_Horizontal
S1J2: Conn_01x20_Socket; MakerDiary_nRF9151_ConnectKit_PinHeader_1-20
S1J3: Conn_01x20_Socket_21-40; MakerDiary_nRF9151_ConnectKit_PinHeader_21-40
S1J4: VCC; PinSocket_1x02_P2.54mm_Vertical
S1R1, S1R2: 4.7K; R_0402_1005Metric
S2C1: CKG57NX7R1H476M500JH 47uF; CAPC6050X550N
S2D1, S2D3: BZX84C15; SOT-23
S2D2, S2D4: PTVS33VS1UTR,115; Nexperia_CFP3_SOD-123W
S2Q1, S2Q2: SQ2361; SOT-23
S2R1, S2R2, S6R3, S7R2: 1M; R_0402_1005Metric
S3C1, S6C2, S15C4: 1uF; C_0402_1005Metric
S3C2, S4C1, S6C1, S8C1, S8C3: 100nF; C_0402_1005Metric
S3U1: INA228; TSSOP-10_3x3mm_P0.5mm
S4Q1, S7Q1: 2N7002; SOT-23
S4R1: 120K; R_0402_1005Metric
S4R2: 47K; R_0402_1005Metric
S4R3: 56K; R_0402_1005Metric
S6C3: 4.7uF; C_0805_2012Metric
S6C4: 10pF; C_0402_1005Metric
S6C5: 22uF; C_0805_2012Metric
S6L1: XFL4020-222ME; IND_XFL4020-222ME
S6R1: 18.2K; R_0402_1005Metric
S6R2: 226K; R_0402_1005Metric
S6U1: LT8609AIMSE_PBF; LT8609AIMSE_WITH_GROUND_VIAS
S6U2, S15U1: LM66100DCK; SOT-363_SC-70-6
S7Q2: DMG3415U; SOT-23
S7R1, S7R3: 100K; R_0402_1005Metric
S7R4: 470K; R_0402_1005Metric
S8C2: 10uF; C_0603_1608Metric
S8U1: ASM330LHHXTR; XDCR_ASM330LHHXTR
S13D1, S13D2, S13D3: LED; LED_0603_1608Metric
S13R1, S13R2, S13R3: 1K; R_0402_1005Metric
S15C1, S15C2: 100pF; C_0402_1005Metric
S15C3: 10nF; C_0402_1005Metric
S15FB1: 600R; L_0402_1005Metric
S15J1: GPS_UFL; U.FL_Hirose_U.FL-R-SMT-1_Vertical
S15J2: GPS_SMA; SAMTEC_SMA-J-P-H-RA-TH1
S15J3: GSM_UFL; U.FL_Hirose_U.FL-R-SMT-1_Vertical
S15J4: GSM_SMA; SAMTEC_SMA-J-P-H-RA-TH1
S15L1: 47-100 nH, SRF > 2 GHz; L_0603_1608Metric

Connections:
ACCELL_INT1: S1J2.15, S8U1.4 (INT1)
ACCELL_INT2: S1J2.17, S8U1.9 (INT2)
AUX_ENABLE: S1J3.32 (Pin_9), S7R1.1
GND: GND1.1 (1_1), S1C1.2, S1C2.2, S1J1.1, S1J2.3 (GND), S1J3.39 (Pin_2), S1J4.2, S2C1.2, S2D2.2 (A), S2D4.2 (A), S2R1.2, S2R2.2, S3C1.1, S3C2.1, S3U1.1 (A1), S3U1.2 (A0), S3U1.7 (GND), S4C1.2, S4Q1.2 (S), S4R2.1, S6C2.2, S6C3.2, S6C5.2, S6R1.2, S6R2.2, S6U1.5 (SYNC), S6U1.11 (GND), S6U2.2 (GND), S6U2.5 (ST), S7Q1.2 (S), S7R2.1, S8C1.2, S8C2.2, S8C3.2, S8U1.1 (SDO/SA0), S8U1.2 (MSDA), S8U1.3 (MSCL), S8U1.6 (NC), S8U1.7 (GND), S8U1.10 (NC), S8U1.11 (NC), S13D1.1 (K), S13D2.1 (K), S13D3.1 (K), S15C2.2, S15C3.2, S15C4.2, S15J1.2 (Ext), S15J2.2, S15J2.3, S15J2.4, S15J2.5, S15J3.2 (Ext), S15J4.2, S15J4.3, S15J4.4, S15J4.5, S15U1.2 (GND), S15U1.5 (ST)
I2C_SCL: S1J3.27 (Pin_14), S1R2.1, S3U1.5 (SCL), S8U1.13 (SCL)
I2C_SDA: S1J3.28 (Pin_13), S1R1.1, S3U1.4 (SDA), S8U1.14 (SDA)
IGN_SENSE: S1J3.33 (Pin_8), S4Q1.3 (D), S4R3.2
INA_ALRT: S1J3.29 (Pin_12), S3U1.3 (~Alert)
LED1: S1J2.20, S13R1.2
LED2: S1J2.19, S13R2.2
LED3: S1J2.18, S13R3.2
unnamed: S2D1.1 (A), S2Q1.1 (G), S2R1.1
unnamed: S2D3.1 (A), S2Q2.1 (G), S2R2.1
unnamed: S4C1.1, S4Q1.1 (G), S4R1.2, S4R2.2
unnamed: S6C1.1, S6U1.1 (BST)
unnamed: S6C4.1, S6R2.1, S6R3.1, S6U1.6 (FB)
unnamed: S6C2.1, S6U1.3 (INTVCC)
unnamed: S6R1.1, S6U1.4 (RT)
unnamed: S6C1.2, S6L1.1, S6U1.2 (SW)
unnamed: S6C4.2, S6C5.1, S6L1.2, S6R3.2, S6U2.1 (VIN)
unnamed: S7Q1.3 (D), S7R3.2
unnamed: S7Q1.1 (G), S7R1.2, S7R2.2
unnamed: S7Q2.1 (G), S7R3.1, S7R4.2
unnamed: S13D1.2 (A), S13R1.1
unnamed: S13D2.2 (A), S13R2.1
unnamed: S13D3.2 (A), S13R3.1
unnamed: S15C2.1, S15C3.1, S15C4.1, S15FB1.2, S15L1.1
unnamed: S15C1.1, S15J1.1 (In)
unnamed: S15J3.1 (In), S15J4.1
PP3V3: PP3V3.1 (1_1), S1J3.40 (Pin_1), S1R1.2, S1R2.2, S3C1.2, S3C2.2, S3U1.6 (VS), S4R3.1, S7Q2.2 (S), S7R4.1, S8C1.1, S8C2.1, S8C3.1, S8U1.5 (VDD_IO), S8U1.8 (VDD), S8U1.12 (CS)
PP3V3_AUX: PP3V3AUX1.1 (1_1), S7Q2.3 (D), S15U1.1 (VIN)
PP3V3_GPS: PP3V3GPS2.1 (1_1), S15FB1.1, S15U1.3 (~CE), S15U1.6 (VOUT)
PP4V2: PP4V5.1 (1_1), S1C1.1, S1C2.1, S1J4.1, S6U2.3 (~CE), S6U2.6 (VOUT)
PP12V: S1J1.3, S2D4.1 (K), S2Q2.3 (D)
PP12VI: S1J1.4, S2D2.1 (K), S2Q1.3 (D)
PP12VIP: PP12VIP1.1 (1_1), S2D1.3 (K), S2Q1.2 (S), S4R1.1
PP12VP: PP12VP1.1 (1_1), S2C1.1, S2D3.3 (K), S2Q2.2 (S), S3U1.8 (Vbus), S3U1.9 (Vin-), S3U1.10 (Vin+), S6C3.1, S6U1.9 (VIN), S6U1.10 (EN/UV)
RF: S15C1.2, S15J2.1, S15L1.2

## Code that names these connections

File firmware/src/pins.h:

#ifndef PINS_H_
#define PINS_H_

/* PCB pin assignments — P0.x GPIO numbers, -1 = not fitted on this board.
 *
 * All values come from Kconfig (APP_PIN_*).  The per-board defaults live in
 * Kconfig.boards, selected by the APP_BOARD choice; a bench or board variant
 * can still remap any signal from local.conf without touching code. */
#define PIN_K1_TX      CONFIG_APP_PIN_K1_TX
#define PIN_K1_RX      CONFIG_APP_PIN_K1_RX
#define PIN_K2_TX      CONFIG_APP_PIN_K2_TX
#define PIN_K2_RX      CONFIG_APP_PIN_K2_RX
#define PIN_L_SEND     CONFIG_APP_PIN_L_SEND
#define PIN_L_RECV     CONFIG_APP_PIN_L_RECV
#define PIN_L_SENSE    CONFIG_APP_PIN_L_SENSE
#define PIN_K_EN       CONFIG_APP_PIN_K_EN
#define PIN_K_SLEEP    CONFIG_APP_PIN_K_SLEEP
#define PIN_AUX_SW     CONFIG_APP_PIN_AUX_SW
#define PIN_OBD_EN     CONFIG_APP_PIN_OBD_EN
#define PIN_CAN_EN     CONFIG_APP_PIN_CAN_EN
#define PIN_TWI_SDA    CONFIG_APP_PIN_TWI_SDA
#define PIN_TWI_SCL    CONFIG_APP_PIN_TWI_SCL
#define PIN_INA_ALRT   CONFIG_APP_PIN_INA_ALRT
#define PIN_ACC_INT1   CONFIG_APP_PIN_ACC_INT1
#define PIN_ACC_INT2   CONFIG_APP_PIN_ACC_INT2
#define PIN_IGN_SENSE  CONFIG_APP_PIN_IGN_SENSE

/* MCP2518FD CAN controller (SPI bit-banged; -1 on boards without CAN) */
#define PIN_CAN_SCK    CONFIG_APP_PIN_CAN_SCK
#define PIN_CAN_SDI    CONFIG_APP_PIN_CAN_SDI
#define PIN_CAN_SDO    CONFIG_APP_PIN_CAN_SDO
#define PIN_CAN_CS     CONFIG_APP_PIN_CAN_CS
#define PIN_CAN_INT    CONFIG_APP_PIN_CAN_INT

/* Status LEDs (-1 = not fitted; LED4/5 exist only on v2.1 mini) */
#define PIN_LED1       CONFIG_APP_PIN_LED1
#define PIN_LED2       CONFIG_APP_PIN_LED2
#define PIN_LED3       CONFIG_APP_PIN_LED3
#define PIN_LED4       CONFIG_APP_PIN_LED4
#define PIN_LED5       CONFIG_APP_PIN_LED5

/* Switched-rail status sense inputs (v3.1+).  The 3.3V senses read high
 * while their rail is up; the 12V sense is inverted by a 2N7002 and reads
 * low while PP12V_K is up (CONFIG_APP_BOARD_RAIL_ST_12V_ACTIVE_LOW). */
#define PIN_GPS_RAIL_ST    CONFIG_APP_PIN_GPS_RAIL_ST
#define PIN_CAN_RAIL_ST    CONFIG_APP_PIN_CAN_RAIL_ST
#define PIN_K3V3_RAIL_ST   CONFIG_APP_PIN_K3V3_RAIL_ST
#define PIN_K12V_RAIL_ST   CONFIG_APP_PIN_K12V_RAIL_ST

/* The AUX domain's rail, as the schematic names it: the GPS antenna bias on
 * boards with the built-in receiver, the whole external receiver on v4.0. */
#ifdef CONFIG_APP_BOARD_HAS_EXT_GNSS
#define GPS_RAIL_NAME  "PP3V3_GNSS"
#else
#define GPS_RAIL_NAME  "PP3V3_GPS"
#endif

/* External GNSS receiver (v4.0): the UART to the MAX-M10S, its 1PPS output
 * and the switch for its backup supply.  -1 where there is none. */
#define PIN_GNSS_TX        CONFIG_APP_PIN_GNSS_TX
#define PIN_GNSS_RX        CONFIG_APP_PIN_GNSS_RX
#define PIN_GNSS_TIMEPULSE CONFIG_APP_PIN_GNSS_TIMEPULSE
#define PIN_GNSS_BCKP_EN   CONFIG_APP_PIN_GNSS_BCKP_EN

/* External SPI NOR flash (MX25R6435F, src/extflash.c), bit-banged.  -1 where
 * there is none.  Named as the flash sees them, like the CAN controller's:
 * SDI is data into the flash.  On the v4.1.x designs they are the CAN
 * controller's bus pins, and only FLASH_CS is its own. */
#define PIN_FLASH_SCK  CONFIG_APP_PIN_FLASH_SCK
#define PIN_FLASH_SDI  CONFIG_APP_PIN_FLASH_SDI
#define PIN_FLASH_SDO  CONFIG_APP_PIN_FLASH_SDO
#define PIN_FLASH_CS   CONFIG_APP_PIN_FLASH_CS

/* 0-30V AIO inputs (v2.1 only) */
#define PIN_AIO1       CONFIG_APP_PIN_AIO1
#define PIN_AIO2       CONFIG_APP_PIN_AIO2
#define PIN_AIO3       CONFIG_APP_PIN_AIO3
#define PIN_AIO4       CONFIG_APP_PIN_AIO4
#define PIN_AIO5       CONFIG_APP_PIN_AIO5
#define PIN_AIO6       CONFIG_APP_PIN_AIO6

/* INA and accelerometer share the TWIM bus */
#define PIN_INA_SDA    PIN_TWI_SDA
#define PIN_INA_SCL    PIN_TWI_SCL
#define PIN_ACC_SDA    PIN_TWI_SDA
#define PIN_ACC_SCL    PIN_TWI_SCL

#endif

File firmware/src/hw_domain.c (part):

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
static void bckp_set(bool on)
{
	if (!IS_ENABLED(CONFIG_APP_GNSS_BACKUP_SUPPLY) || PIN_GNSS_BCKP_EN < 0 ||
	    on == s_bckp_on) {
		return;
	}
	gpio_pin_configure(hw_gpio0, PIN_GNSS_BCKP_EN,
			   on ? GPIO_OUTPUT_HIGH : GPIO_OUTPUT_LOW);
	s_bckp_on = on;
	bklog_note(on);
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
static void dom_add_can_pins(struct domain *d)
{
	dom_add(d, PIN_CAN_SCK, ROLE_OUT_LOW);
	dom_add(d, PIN_CAN_SDI, ROLE_OUT_LOW);
	dom_add(d, PIN_CAN_SDO, ROLE_IN);
	dom_add(d, PIN_CAN_CS,  ROLE_IN);      /* 10K pull-up on the CAN rail */
	dom_add(d, PIN_CAN_INT, ROLE_IN);      /* 10K pull-up on the CAN rail */
}

static void dom_add_kline_pins(struct domain *d)
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	 * internal pull-up, and the UARTE drives the pin once the driver opens
	 * it, which is after the rail is up. */
	if (IS_ENABLED(CONFIG_APP_BOARD_HAS_EXT_GNSS)) {
		dom_add(aux, PIN_GNSS_TX,        ROLE_IN);
		dom_add(aux, PIN_GNSS_RX,        ROLE_IN);
		dom_add(aux, PIN_GNSS_TIMEPULSE, ROLE_IN);
	}

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	 * APP_GNSS_BACKUP_OFF_UTC_HOUR if that is set, and comes back with the
	 * receiver's rail: it is what lets the receiver hot-start
	 * (APP_GNSS_BACKUP_SUPPLY). */
	if (IS_ENABLED(CONFIG_APP_BOARD_HAS_EXT_GNSS) && PIN_GNSS_BCKP_EN >= 0) {
		/* Up from boot; a server that wants it dropped says so in its
		 * first reply (hw_gnss_backup_want()). */
		s_bckp_on = IS_ENABLED(CONFIG_APP_GNSS_BACKUP_SUPPLY);
		gpio_pin_configure(hw_gpio0, PIN_GNSS_BCKP_EN,
				   s_bckp_on ? GPIO_OUTPUT_HIGH : GPIO_OUTPUT_LOW);
		/* Not noted: coming up is not a change, and the server holds the
		 * state.  A note here read as "it is on" and overrode a server
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
		dom_rail_sense(aux, PIN_GPS_RAIL_ST,  false,   GPS_RAIL_NAME,
			       true);
		dom_rail_sense(can, PIN_CAN_RAIL_ST,  false,   "PP3V3_CAN",
			       has_can);
		dom_rail_sense(k,   PIN_K3V3_RAIL_ST, false,   "PP3V3_K",
			       has_k);
		dom_rail_sense(k,   PIN_K12V_RAIL_ST, inv_12v, "PP12V_K",
			       has_k);
	}

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	bool was_on = s_bckp_on;
	bool was_hold = s_bckp_hold;

	if (!IS_ENABLED(CONFIG_APP_GNSS_BACKUP_SUPPLY) || PIN_GNSS_BCKP_EN < 0) {
		return false;
	}
	s_bckp_hold = !on;
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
